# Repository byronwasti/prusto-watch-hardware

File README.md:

# Prusto Watch Hardware
Hardware for the Prusto Watch

# Update Log

## 0.3.0
- Chip now has USB functionality
- Moved to an accelerometer instead of an IMU
- New PMIC chip
- Smaller layout with mounting holes

## 0.2.0
- Chip selected has no USB functionality
- LEDs work
- Battery connector is incorrect
- BLE is functional
- Display connector is flipped (must be soldered on backwards)

## 0.1.0
- Poor debuggability
- BLE connectivity
- IMU routing
- LED
- Display

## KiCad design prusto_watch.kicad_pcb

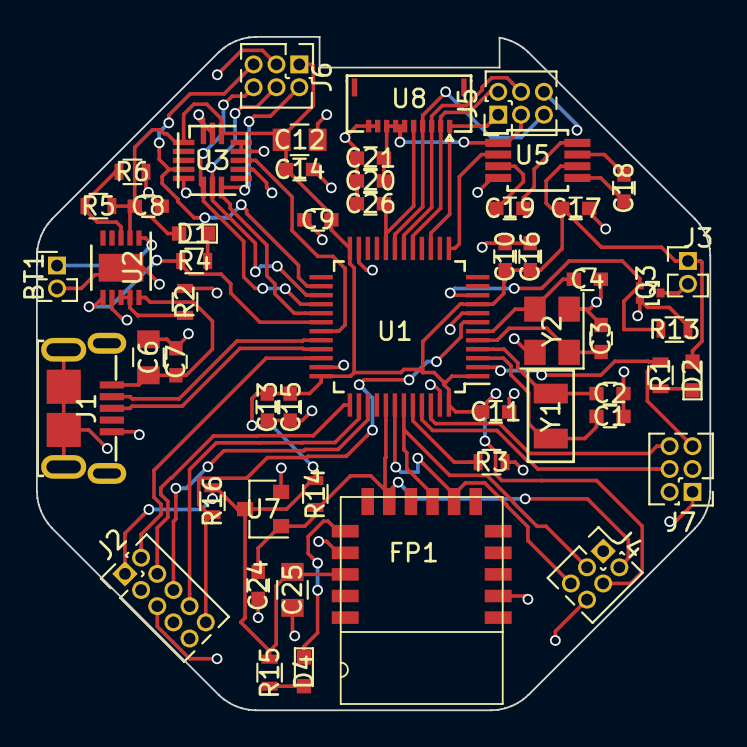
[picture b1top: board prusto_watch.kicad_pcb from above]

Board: 2 copper layers, 37.4 x 37.4 mm, 54 parts (0 on the bottom side), 47 nets.

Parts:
BT1: RJD3032HPPV30M; Pin_Header_Straight_1x02_Pitch1.27mm
C1, C2: 12.5pF; C_0603
C3, C4: 18pF; C_0603
C6, C12, C25: 10uF; C_0805
C7, C17, C18, C19, C21, C24: 1uF; C_0603
C8: 2.2uF; C_0603
C9, C10, C11, C13, C14, C15, C16, C20, C26: 100nF; C_0603
D1, D2, D4: LED; LED_0603
FP1: RN4871; BM71BLES1FC2
J1: USB_microB_2040002-1
J2: Conn_02x05_Odd_Even; Pin_Header_Straight_2x05_Pitch1.27mm
J3: Vibration Motor; Pin_Header_Straight_1x02_Pitch1.27mm
J4, J5: Conn_01x06; Pin_Header_Straight_2x03_Pitch1.27mm
J6: Conn_02x03_Odd_Even; Pin_Header_Straight_2x03_Pitch1.27mm
J7: Conn_02x03_Counter_Clockwise; Pin_Header_Straight_2x03_Pitch1.27mm
Q3: RUM002N02T2L; VMT3
R1, R4, R15: 1K; R_0603
R2, R3, R16: 10K; R_0603
R5: 301K; R_0603
R6, R13: 100K; R_0603
R14: 4.75K; R_0603
U1: STM32F303RCT6-48; LQFP-48_7x7mm_Pitch0.5mm
U2: LTC4063; DFN-10-1EP_3x3mm_Pitch0.5mm
U3: LIS3DETR; 16-LGA_(3x3)
U5: TPS60241DGKR; MSOP-8_3x3mm_Pitch0.65mm
U7: RT9818A-18GV; SOT-23
U8: WM1389CT-ND; Molex_FPC_5034801000
Y1: ECS.327; ECX-31B
Y2: FA-238; Crystal_SMD_SeikoEpson_FA238V-4pin_3.2x2.5mm

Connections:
+3V3: C8.1, C9.1, C10.1, C11.1, C12.1, C13.1, C14.1, C15.1, C16.1, C17.1, C25.2, D1.2, D2.2, FP1.14, J2.1, J3.1, J4.4, J6.1, R5.1, R14.1, R15.1, R16.1, U1.1, U1.9, U1.24, U1.36, U1.48, U2.2, U3.1, U3.14, U5.6, U7.3
+5V: C20.1, C21.1, J5.3, U5.1, U8.6, U8.7, U8.8
/5V_EN: U1.13, U5.2
/ACC_CS: J6.2, U1.29, U3.8
/ACC_INT1: U1.31, U3.11
/ACC_SCK: J6.5, U1.26, U3.4
/ACC_SDI: J6.6, U1.28, U3.6
/ACC_SDO: J6.4, U1.27, U3.7
/BLE_nRST: C24.1, FP1.10, J4.2, R14.2, U1.41, U7.1
/BUTTON1: J7.4, U1.45
/BUTTON2: J7.6, U1.46
/CHRG_STAT: R4.2, U1.30, U2.6
/DISP_EN: C26.1, U1.20, U8.5
/DISP_SCLK: J5.1, U1.15, U8.1
/DISP_SCS: J5.4, U1.18, U8.3
/DISP_SDI: J5.2, U1.17, U8.2
/EXTCOMIN: J5.5, U1.19, U8.4
/LED_1: J7.5, R1.2, U1.2
/MOTOR_EN: Q3.1, R13.1, U1.10
/RX_BLE: FP1.7, J4.5, U1.42
/STM_NRST: J2.10, R16.2, U1.7
/TCK: J2.4, U1.37
/TDI: J2.8, U1.38
/TDO: J2.6, U1.39
/TMS: J2.2, U1.34
/TX_BLE: FP1.8, J4.3, U1.43
/USB_N: J1.2, U1.32
/USB_P: J1.3, U1.33
GND: BT1.2, C1.2, C2.2, C3.2, C4.2, C6.2, C7.2, C8.2, C9.2, C10.2, C11.2, C12.2, C13.2, C14.2, C15.2, C16.2, C17.2, C20.2, C21.2, C24.2, C25.1, C26.2, FP1.2, FP1.13, J1.5, J1.6, J1.7, J1.8, J1.9, J1.10, J1.11, J2.3, J2.5, J4.6, J5.6, J6.3, J7.1, J7.2, J7.3, Q3.2, R2.2, R3.2, R6.2, R13.2, U1.8, U1.23, U1.35, U1.47, U2.7, U2.11, U3.5, U3.10, U3.12, U3.13, U3.15, U3.16, U5.4, U7.2, U8.9, U8.10, Y2.2, Y2.4
unnamed: BT1.1, U2.1
unnamed: C1.1, U1.3, Y1.2
unnamed: C2.1, U1.4, Y1.1
unnamed: C3.1, U1.5, Y2.1
unnamed: C4.1, U1.6, Y2.3
unnamed: C6.1, C7.1, J1.1, U2.10
unnamed: C18.1, U5.7
unnamed: C18.2, U5.5
unnamed: C19.1, U5.8
unnamed: C19.2, U5.3
unnamed: D1.1, R4.1
unnamed: D2.1, R1.1
unnamed: D4.1, FP1.12
unnamed: D4.2, R15.2
unnamed: J3.2, Q3.3
unnamed: R2.1, U2.8, U2.9
unnamed: R3.1, U1.44
unnamed: R5.2, R6.1, U2.3

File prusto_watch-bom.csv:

Reference, Quantity, Value, Footprint, Datasheet, Digikey
BT1 ,1,"RJD3032HPPV30M","Pin_Headers:Pin_Header_Straight_1x02_Pitch1.27mm","","1572-1623-ND"
C1 C2 ,2,"12.5pF","Capacitors_SMD:C_0603",""
C17 C18 C19 C21 C24 C7 ,6,"1uF","Capacitors_SMD:C_0603",""
C12 C25 C6 ,3,"10uF","Capacitors_SMD:C_0805",""
C3 C4 ,2,"18pF","Capacitors_SMD:C_0603",""
C8 ,1,"2.2uF","Capacitors_SMD:C_0603",""
C10 C11 C13 C14 C15 C16 C20 C26 C9 ,9,"100nF","Capacitors_SMD:C_0603",""
D1 D2 D4 ,3,"LED","LEDs:LED_0603",""
FP1 ,1,"RN4871","prusto_watch:BM71BLES1FC2",""
J1 ,1,"USB_microB_2040002-1","prusto_watch:USB_microB_2040002-1","","TODO"
J2 ,1,"Conn_02x05_Odd_Even","Pin_Headers:Pin_Header_Straight_2x05_Pitch1.27mm",""
J3 ,1,"Vibration Motor","Pin_Headers:Pin_Header_Straight_1x02_Pitch1.27mm",""
J4 J5 ,2,"Conn_01x06","Pin_Headers:Pin_Header_Straight_2x03_Pitch1.27mm",""
J6 ,1,"Conn_02x03_Odd_Even","Pin_Headers:Pin_Header_Straight_2x03_Pitch1.27mm",""
J7 ,1,"Conn_02x03_Counter_Clockwise","Pin_Headers:Pin_Header_Straight_2x03_Pitch1.27mm",""
Q3 ,1,"RUM002N02T2L","prusto_watch:VMT3",""
R13 R6 ,2,"100K","Resistors_SMD:R_0603",""
R14 ,1,"4.75K","Resistors_SMD:R_0603",""
R1 R15 R4 ,3,"1K","Resistors_SMD:R_0603",""
R16 R2 R3 ,3,"10K","Resistors_SMD:R_0603",""
R5 ,1,"301K","Resistors_SMD:R_0603",""
U1 ,1,"STM32F303RCT6-48","Housings_QFP:LQFP-48_7x7mm_Pitch0.5mm","","497-15198-ND"
U2 ,1,"LTC4063","prusto_watch:DFN-10-1EP_3x3mm_Pitch0.5mm",""
U3 ,1,"LIS3DETR","prusto_watch:16-LGA_(3x3)",""
U5 ,1,"TPS60241DGKR","Housings_SSOP:MSOP-8_3x3mm_Pitch0.65mm","","TODO"
U7 ,1,"RT9818A-18GV","TO_SOT_Packages_SMD:SOT-23",""
U8 ,1,"WM1389CT-ND","prusto_watch:Molex_FPC_5034801000",""
Y1 ,1,"ECS.327","prusto_watch:ECX-31B",""
Y2 ,1,"FA-238","Crystals:Crystal_SMD_SeikoEpson_FA238V-4pin_3.2x2.5mm",""

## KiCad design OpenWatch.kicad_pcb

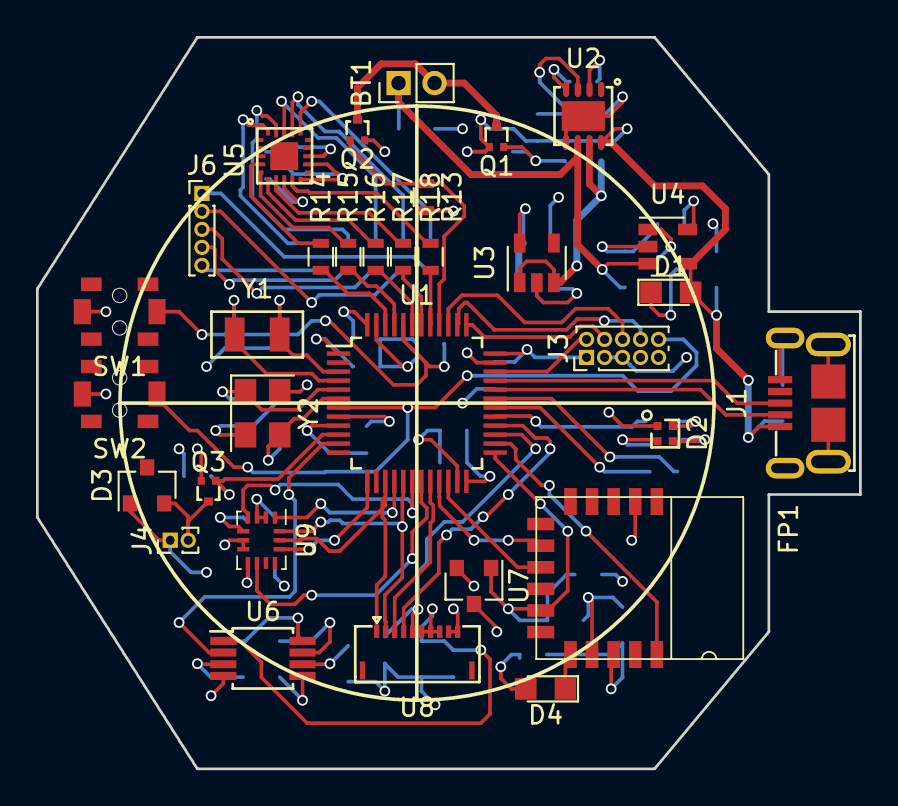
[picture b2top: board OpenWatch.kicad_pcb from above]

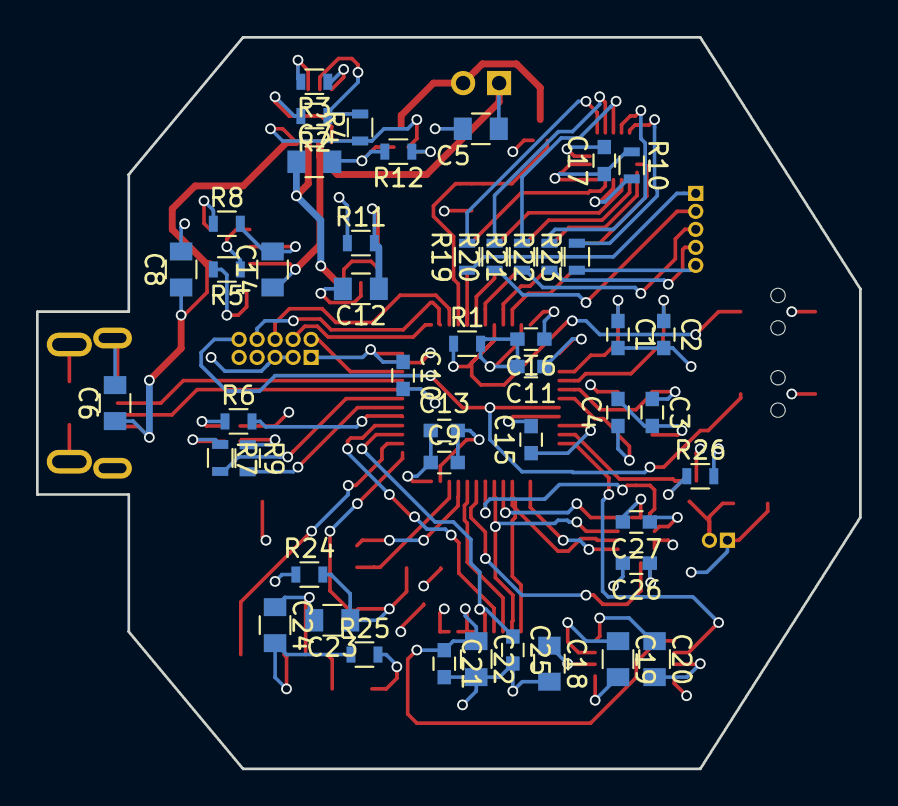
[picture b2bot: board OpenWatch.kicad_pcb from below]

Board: 4 copper layers, 45.7 x 40.6 mm, 79 parts (47 on the bottom side), 75 nets.

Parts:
BT1: Battery_Cell; Pin_Header_Straight_1x02_Pitch2.00mm
C1, C2: 12.5pF; C_0603
C3, C4: 18pF; C_0603
C5, C8, C14: 4.7uF; C_0805
C6, C24: 10uF; C_0805
C7, C18, C19, C20, C22, C23: 1uF; C_0805
C9, C10, C11, C13, C15, C16, C17, C21, C25, C26, C27: 100nF; C_0603
C12: 2.2uF; C_0805
D1, D4: LED; LED_0805
D2: LED_ARGB; SMLP34RGB2W3
D3: BAT54; SOT-23
FP1: BM71BLES1FC2
J1: USB_microB_2040002-1
J3: Conn_02x05_Odd_Even; Pin_Header_Straight_2x05_Pitch1.00mm
J4: Vibration Motor; Pin_Header_Straight_1x02_Pitch1.00mm
J6: Conn_01x05; Pin_Header_Straight_1x05_Pitch1.00mm
Q1, Q2, Q3: RUM002N02T2L; VMT3
R1, R8, R10, R14, R15, R16, R17, R18, R19, R20, R21, R22, R23: 10K; R_0603
R2, R12, R13, R26: 100K; R_0603
R3: 402; R_0603
R4: 200K; R_0603
R5: 470; R_0603
R6, R7, R9, R25: 1K; R_0603
R11: DNP-0; R_0603
R24: 4.75K; R_0603
SW1, SW2: SW_Push; PTS820_J15M_SMTR_LFS
U1: STM32F303RCT6-48; LQFP-48_7x7mm_Pitch0.5mm
U2: TPS2113ADRBR; SON-8
U3: TSP70933DBVR; SOT-23-5
U4: MCP73831T-2ACI; SOT-23-5
U5: AT42QT1070-MMHR
U6: TPS60241DGKR; MSOP-8_3x3mm_Pitch0.65mm
U7: RT9818A-18GV; SOT-23
U8: WM1389CT-ND; Molex_FPC_5034801000
U9: LSM6DSL; Bosch_LGA-14_3x2.5mm_Pitch0.5mm
Y1: ECS.327; ECX-31B
Y2: FA-238; Crystal_SMD_SeikoEpson_FA238V-4pin_3.2x2.5mm

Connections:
+3V3: C9.1, C10.1, C11.1, C13.1, C15.1, C16.1, C17.1, C18.1, C24.2, C26.1, C27.1, D2.1, D3.1, FP1.14, J3.1, J4.1, R10.1, R11.1, R24.1, R25.1, SW1.1, U1.1, U1.9, U1.24, U1.36, U1.48, U5.9, U5.11, U6.6, U7.3, U9.5, U9.8
+5V: C21.1, C22.1, U6.1, U8.6, U8.7, U8.8
/5V_EN: U1.11, U6.2
/BATT_EN: Q2.1, R13.1, U1.40
/BLE_CONF: FP1.16, U1.26
/BLE_nRST: C23.1, FP1.10, R24.2, U1.25, U7.1
/DISP_EN: C25.1, U1.27, U8.5
/DISP_SCLK: U1.15, U8.1, U9.13
/DISP_SCS: U1.20, U8.3
/DISP_SDI: U1.17, U8.2, U9.14
/D_N: J1.2, U1.32
/D_P: J1.3, U1.33
/EXTCOMIN: U1.28, U8.4
/IMU_CS: U1.13, U9.12
/IMU_INT_1: U1.18, U9.4
/IMU_INT_2: U1.19, U9.9
/IMU_SDO: U1.16, U9.1
/KEY_0: J6.1, R19.1
/KEY_1: J6.2, R20.1
/KEY_2: J6.3, R21.1
/KEY_3: J6.4, R22.1
/KEY_4: J6.5, R23.1
/LED_BLUE: R7.2, U1.31
/LED_GREEN: R9.2, U1.30
/LED_RED: R6.2, U1.29
/MOTOR_EN: Q3.1, R26.1, U1.10
/NRST_TOUCH: R10.2, U5.13
/RX_BLE: FP1.7, U1.21
/STM_NRST: J3.10, SW2.2, U1.7
/TCK: J3.4, U1.37
/TDI: J3.8, U1.38
/TDO: J3.6, U1.39
/TMS: J3.2, U1.34
/TOUCH_0: R18.1, U1.41
/TOUCH_1: R14.1, U1.46
/TOUCH_2: R15.1, U1.45
/TOUCH_3: R16.1, U1.43
/TOUCH_4: R17.1, U1.42
/TX_BLE: FP1.8, U1.22
/VBATT: BT1.1, C5.1, C14.1, U2.6, U4.3
/VUSB: C6.1, C8.1, D1.2, J1.1, Q1.1, R4.1, R12.1, U2.8, U4.4
GND: C1.2, C2.2, C3.2, C4.2, C5.2, C6.2, C7.2, C8.2, C9.2, C10.2, C11.2, C12.2, C13.2, C14.2, C15.2, C16.2, C17.2, C18.2, C21.2, C22.2, C23.2, C24.1, C25.2, C26.2, C27.2, FP1.2, FP1.13, J1.5, J1.6, J1.7, J1.8, J1.9, J1.10, J1.11, J3.3, J3.5, Q1.2, Q2.2, Q3.2, R1.2, R2.2, R3.2, R8.2, R12.2, R13.2, R26.2, SW2.1, U1.8, U1.23, U1.35, U1.47, U2.2, U2.5, U3.2, U4.2, U5.8, U6.4, U7.2, U8.9, U8.10, U9.2, U9.3, U9.6, U9.7, Y2.2, Y2.4
unnamed: BT1.2, Q1.3, Q2.3
unnamed: C1.1, U1.3, Y1.2
unnamed: C2.1, U1.4, Y1.1
unnamed: C3.1, U1.5, Y2.1
unnamed: C4.1, U1.6, Y2.3
unnamed: C7.1, U2.7, U3.1, U3.3
unnamed: C12.1, R11.2, U3.5
unnamed: C19.1, U6.7
unnamed: C19.2, U6.5
unnamed: C20.1, U6.8
unnamed: C20.2, U6.3
unnamed: D1.1, R5.2
unnamed: D2.2, R6.1
unnamed: D2.3, R7.1
unnamed: D2.4, R9.1
unnamed: D3.2, J4.2, Q3.3
unnamed: D4.1, FP1.12
unnamed: D4.2, R25.2
unnamed: R1.1, SW1.2, U1.44
unnamed: R2.1, R4.2, U2.3
unnamed: R3.1, U2.4
unnamed: R5.1, U4.1
unnamed: R8.1, U4.5
unnamed: R14.2, U5.17
unnamed: R15.2, U5.16
unnamed: R16.2, U5.15
unnamed: R17.2, U5.14
unnamed: R18.2, U5.12
unnamed: R19.2, U5.5
unnamed: R20.2, U5.4
unnamed: R21.2, U5.3
unnamed: R22.2, U5.2
unnamed: R23.2, U5.1

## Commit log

2018-01-31 Add intial files
2018-02-09 Rename to Prusto Watch
2018-02-09 Remove external touch-sensor chip dependency
2018-02-12 Rework component list
2018-02-12 Basic positioning
2018-02-13 Remove battery control circuitry
2018-02-20 Add debug lines and TSC lines
2018-02-20 Update footprints
2018-02-20 Finish basic placement
2018-02-23 Finish routing traces
2018-03-01 Fix table rendering
2018-03-25 Update schematic and README
2018-03-25 Fix footprint for FPC connector
2018-03-29 Add kipart files
2018-03-29 Add new accelerometer and PMIC to library
2018-03-29 Modify schematic
2018-03-30 Finish schematic for v3
2018-03-30 Modify names
2018-03-30 First pass at PCB placement
2018-03-30 Modify for better positioning
2018-04-01 Rework placement
2018-04-01 Switch PMIC with USB input
2018-04-01 Finalize Routing
2018-04-01 Add logos
2018-04-01 Widen power traces
2018-04-21 Update schematic and PCB shape
2018-04-23 Update board layout
2018-04-23 Breakout EXTCOMIN instead of 5Ven
2018-04-23 Update silkscreen
2018-04-24 Finish v0.4
2018-04-25 Update Case
2018-04-25 Update case code style
2018-04-25 Update to case
2018-04-26 Add case v2
2018-04-30 Update BOM with button
2018-05-06 Small changes
